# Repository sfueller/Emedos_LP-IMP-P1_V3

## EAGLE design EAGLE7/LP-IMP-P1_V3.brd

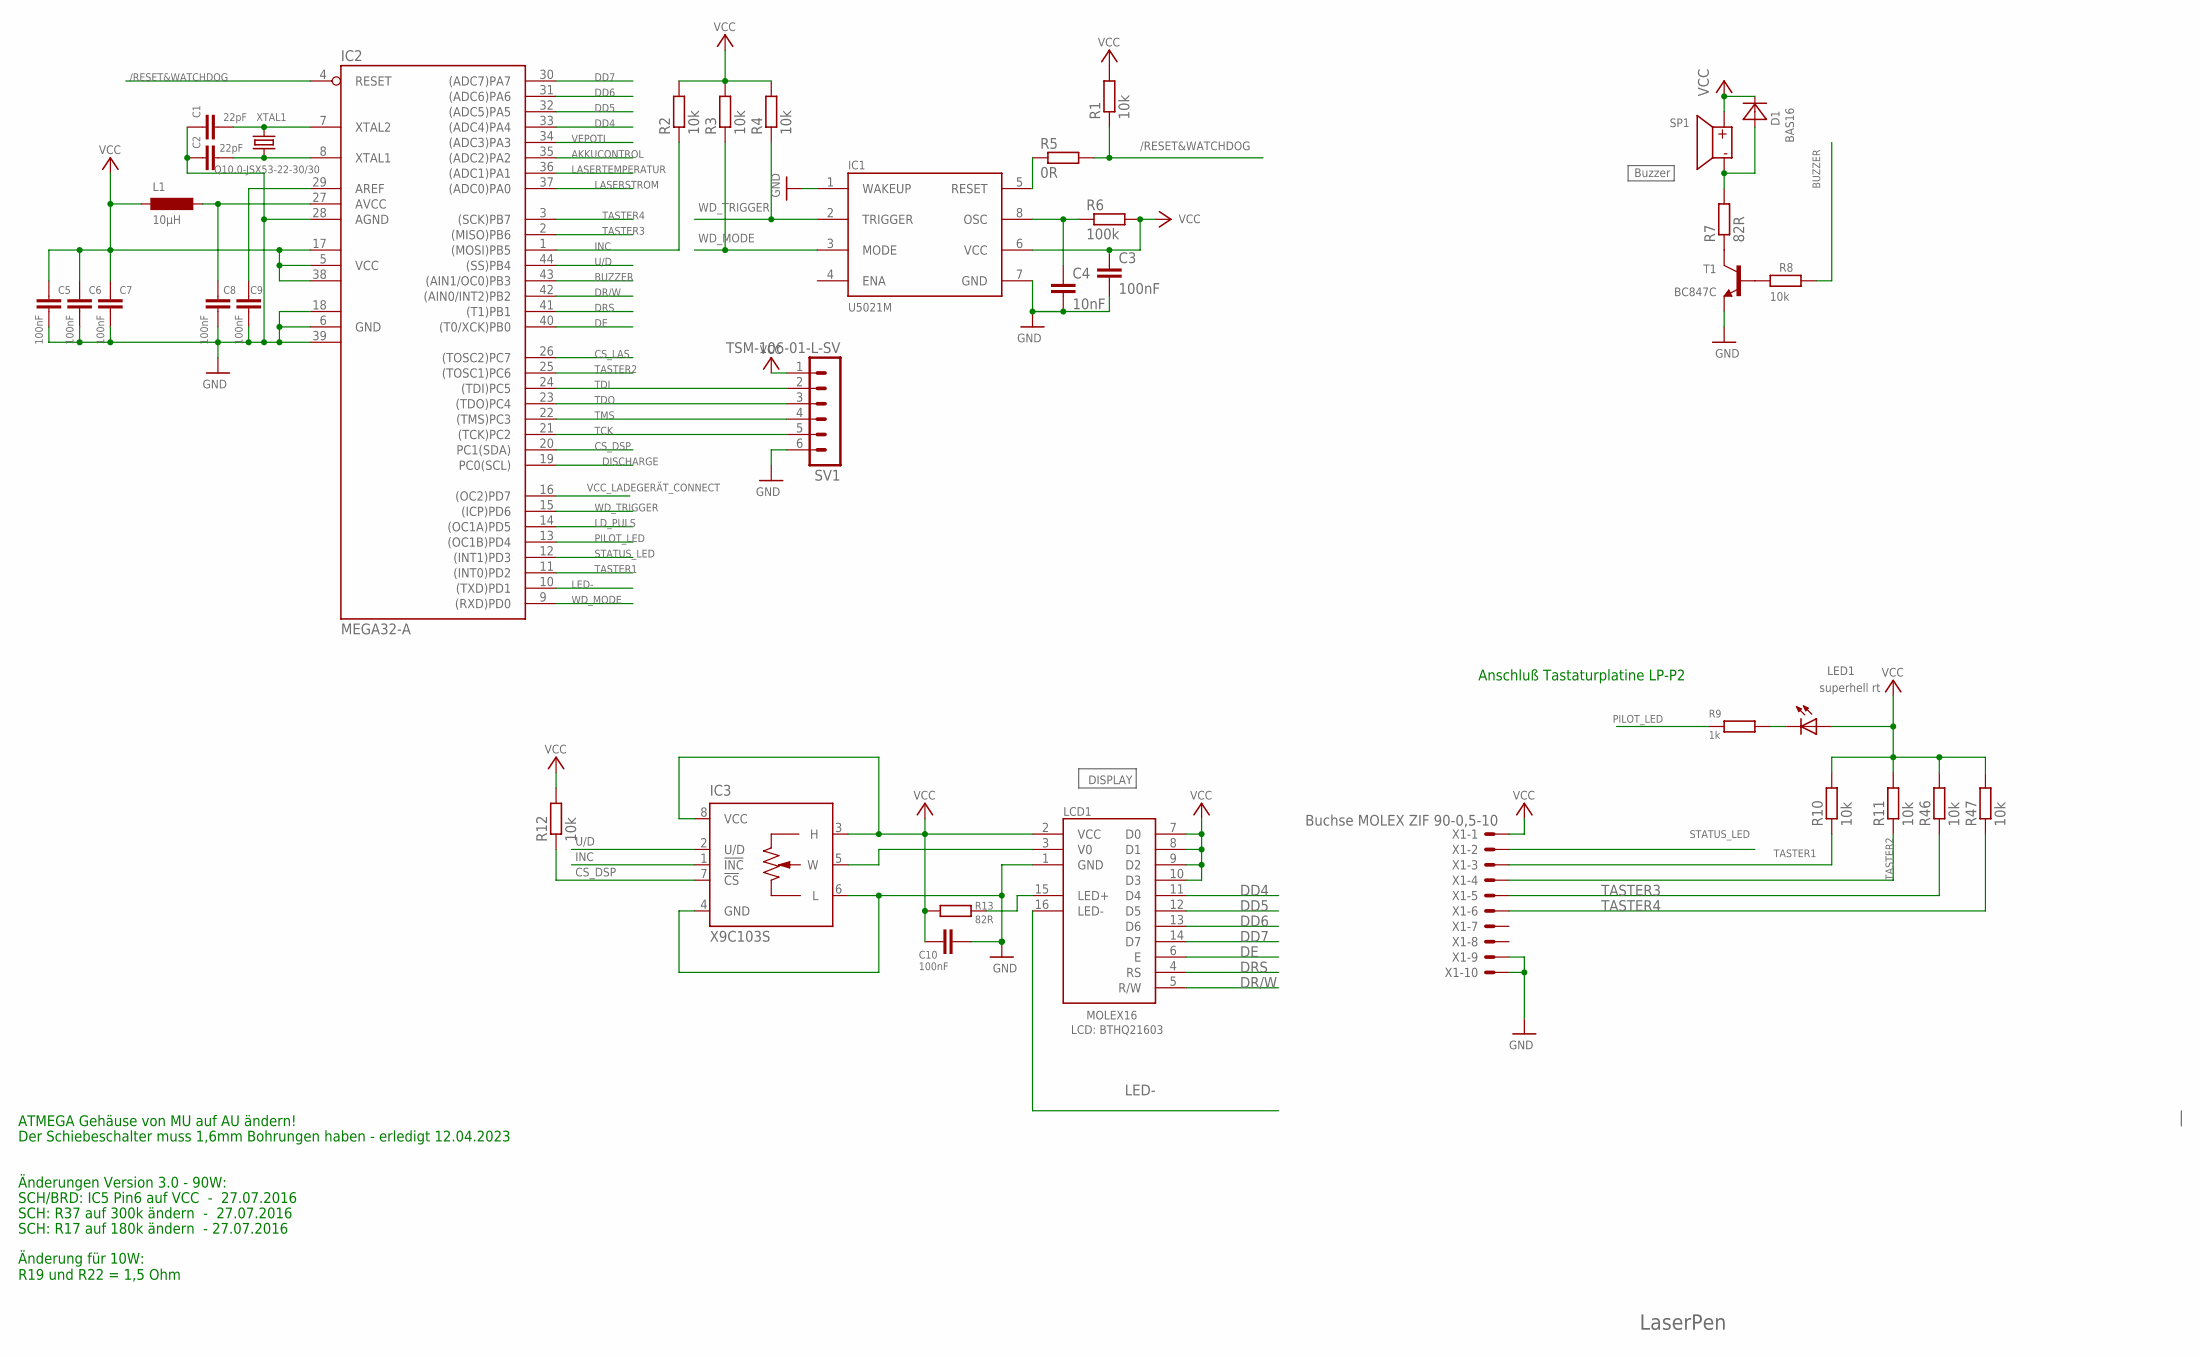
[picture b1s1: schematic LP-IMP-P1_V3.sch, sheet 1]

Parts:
C1, C2: 22pF; C0603
C3, C5, C6, C7, C8, C9, C10: 100nF; C0603
C4: 10nF; C0603
D1: BAS16; DIODE_SOT23
IC1: U5021M; SOIC8
IC2: MEGA32-A; TQFP44
IC3: X9C103S; SOIC08
L1: 10µH; R1210
LCD1: MOLEX16; MOLEX
LED1: superhell rt; LED3MM
R1, R2, R3, R4, R8, R10, R11, R12, R46, R47: 10k; R0603
R5: 0R; R0603
R6: 100k; R0603
R7, R13: 82R; MINI_MELF-0204R
R9: 1k; R0603
SP1: BUZZER
SV1: TSM-106-01-L-SV; MA06-1-SMD
T1: BC847C; SOT23
X1: Buchse MOLEX ZIF 90-0,5-10; 52745-1090
XTAL1: Q10.0-JSX53-22-30/30; JSX53

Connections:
/RESET&WATCHDOG: IC2.4 (RESET), R1.1, R5.2
AKKUCONTROL: IC2.35 ((ADC2)PA2); also elsewhere on the board
AREF: C9.1, IC2.29 (AREF)
AVCC: C8.1, IC2.27 (AVCC), L1.1
BUZZER: IC2.43 ((AIN1/OC0)PB3), R8.1
CS_DSP: IC2.20 (PC1(SDA)), IC3.7 (!CS), R12.1
CS_LAS: IC2.26 ((TOSC2)PC7); also elsewhere on the board
DD4: IC2.33 ((ADC4)PA4), LCD1.11 (D4)
DD5: IC2.32 ((ADC5)PA5), LCD1.12 (D5)
DD6: IC2.31 ((ADC6)PA6), LCD1.13 (D6)
DD7: IC2.30 ((ADC7)PA7), LCD1.14 (D7)
DE: IC2.40 ((T0/XCK)PB0), LCD1.6 (E)
DISCHARGE: IC2.19 (PC0(SCL)); also elsewhere on the board
DR/W: IC2.42 ((AIN0/INT2)PB2), LCD1.5 (R/W)
DRS: IC2.41 ((T1)PB1), LCD1.4 (RS)
GND: C1.1, C2.1, C3.2, C4.2, C5.2, C6.2, C7.2, C8.2, C9.2, C10.1, IC1.1 (WAKEUP), IC1.7 (GND), IC2.6 (GND), IC2.18 (GND1), IC2.28 (AGND), IC2.39 (GND2), IC3.4 (GND), IC3.6 (L), LCD1.1 (GND), SV1.6, T1.2 (E), X1.9, X1.10; also elsewhere on the board
INC: IC2.1 ((MOSI)PB5), IC3.1 (!INC), R2.1; also elsewhere on the board
LASERSTROM: IC2.37 ((ADC0)PA0); also elsewhere on the board
LASERTEMPERATUR: IC2.36 ((ADC1)PA1); also elsewhere on the board
LD_PULS: IC2.14 ((OC1A)PD5); also elsewhere on the board
LED+: LCD1.15 (LED+), R13.2
LED-: IC2.10 ((TXD)PD1), LCD1.16 (LED-)
unnamed: R7.1, T1.3 (C)
unnamed: C1.2, IC2.7 (XTAL2), XTAL1.3 (2)
unnamed: IC1.5 (RESET), R5.1
unnamed: C4.1, IC1.8 (OSC), R6.1
unnamed: LED1.K (C), R9.2
unnamed: C2.2, IC2.8 (XTAL1), XTAL1.1
unnamed: D1.1 (A), R7.2, SP1.-
unnamed: R8.2, T1.1 (B)
PILOT_LED: IC2.13 ((OC1B)PD4), R9.1
STATUS_LED: IC2.12 ((INT1)PD3), X1.2
TASTER1: IC2.11 ((INT0)PD2), R10.1, X1.3
TASTER2: IC2.25 ((TOSC1)PC6), R11.1, X1.4
TASTER3: IC2.2 ((MISO)PB6), R46.1, X1.5
TASTER4: IC2.3 ((SCK)PB7), R47.1, X1.6
TCK: IC2.21 ((TCK)PC2), SV1.5
TDI: IC2.24 ((TDI)PC5), SV1.2
TDO: IC2.23 ((TDO)PC4), SV1.3
TMS: IC2.22 ((TMS)PC3), SV1.4
U/D: IC2.44 ((SS)PB4), IC3.2 (U/D); also elsewhere on the board
V0: IC3.5 (W), LCD1.3 (V0)
VCC: C3.1, C5.1, C6.1, C7.1, C10.2, D1.3 (C), IC1.6 (VCC), IC2.5 (VCC), IC2.17 (VCC1), IC2.38 (VCC2), IC3.3 (H), IC3.8 (VCC), L1.2, LCD1.2 (VCC), LCD1.7 (D0), LCD1.8 (D1), LCD1.9 (D2), LCD1.10 (D3), LED1.A, R1.2, R2.2, R3.2, R4.2, R6.2, R10.2, R11.2, R12.2, R13.1, R46.2, R47.2, SP1.+, SV1.1, X1.1; also elsewhere on the board
VCC_LADEGERÄT_CONNECT: IC2.16 ((OC2)PD7); also elsewhere on the board
VEPOTI: IC2.34 ((ADC3)PA3); also elsewhere on the board
WD_MODE: IC1.3 (MODE), IC2.9 ((RXD)PD0), R3.1
WD_TRIGGER: IC1.2 (TRIGGER), IC2.15 ((ICP)PD6), R4.1

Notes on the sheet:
Buzzer
DISPLAY
LCD: BTHQ21603
LaserPen
Anschluß Tastaturplatine LP-P2
Änderungen Version 3.0 - 90W:
SCH/BRD: IC5 Pin6 auf VCC - 27.07.2016
SCH: R37 auf 300k ändern - 27.07.2016
SCH: R17 auf 180k ändern - 27.07.2016
Änderung für 10W: R19 und R22 = 1,5 Ohm
Der Schiebeschalter muss 1,6mm Bohrungen haben - erledigt 12.04.2023
ATMEGA Gehäuse von MU auf AU ändern!

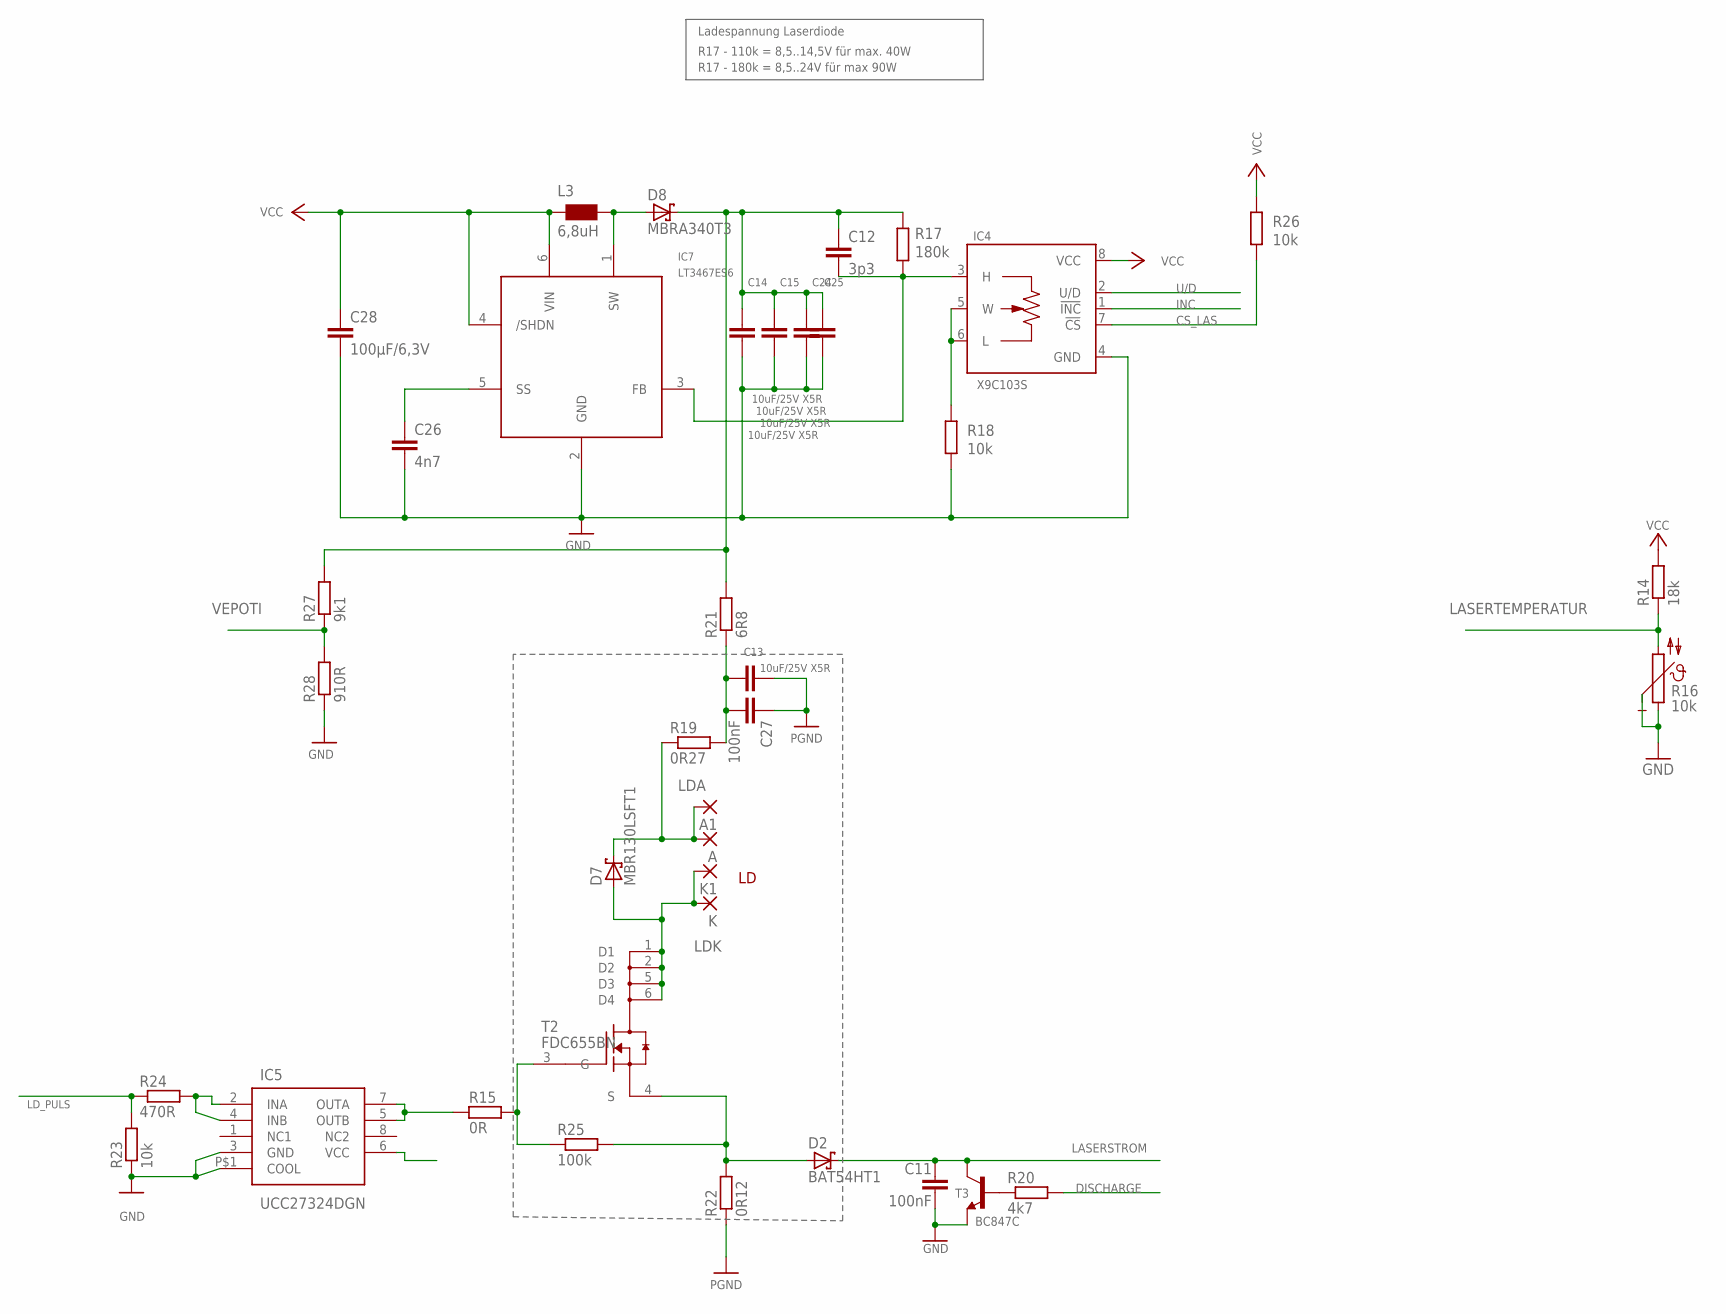
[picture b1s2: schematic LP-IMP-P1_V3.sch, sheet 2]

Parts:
A, A1: WIREPADSMD1,27-254; SMD1,27-2,54
C11, C27: 100nF; C0603
C12: 3p3; C0603
C13, C14, C15, C24, C25: 10uF/25V X5R; C1210K
C26: 4n7; C0603K
C28: 100µF/6,3V; C1210K
D2: BAT54HT1; SOD-323
D7: MBR130LSFT1; SOD-123LF
D8: MBRA340T3; SMA
IC4: X9C103S; SOIC08
IC5: UCC27324DGN; R-PDSO-G8
IC7: LT3467ES6; TSOT-23-6
K, K1: WIREPADSMD1,27-254; SMD1,27-2,54
L3: 6,8uH; WE-PD2_S
R14: 18k; R0603
R15: 0R; MINI_MELF-0204R
R16: 10k; R0805
R17: 180k; R0603
R18, R23, R26: 10k; R0603
R19: 0R27; MINI_MELF-0204R
R20: 4k7; R0603
R21: 6R8; MINI_MELF-0204R
R22: 0R12; MINI_MELF-0204R
R24: 470R; R0603
R25: 100k; R0603
R27: 9k1; R0603
R28: 910R; R0603
T2: FDC655BN; SUPERSOT-6
T3: BC847C; SOT23-BEC

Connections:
CS_LAS: IC4.7 (!CS), R26.1; also elsewhere on the board
DISCHARGE: R20.2; also elsewhere on the board
GND: C11.2, C13.2, C14.2, C15.2, C24.2, C25.2, C26.2, C27.1, C28.2, IC4.4 (GND), IC5.3 (GND), IC5.P$1 (COOL), IC7.2 (GND), R16.1, R18.1, R22.1, R23.1, R28.1, T3.E; also elsewhere on the board
INC: IC4.1 (!INC); also elsewhere on the board
LASERSTROM: C11.1, D2.C, T3.C; also elsewhere on the board
LASERTEMPERATUR: R14.1, R16.2; also elsewhere on the board
LDA: A.1, A1.1, D7.C, R19.1
LDK: D7.A, K.1, K1.1, T2.1 (D1), T2.2 (D2), T2.5 (D3), T2.6 (D4)
LD_PULS: R23.2, R24.1; also elsewhere on the board
unnamed: IC5.5 (OUTB), IC5.7 (OUTA), R15.1
unnamed: IC5.2 (INA), IC5.4 (INB), R24.2
unnamed: IC4.5 (W), IC4.6 (L), R18.2
unnamed: R20.1, T3.B
unnamed: C26.1, IC7.5 (SS)
unnamed: R15.2, R25.1, T2.3 (G)
unnamed: D8.A, IC7.1 (SW), L3.1 (2)
unnamed: C13.1, C27.2, R19.2, R21.1
unnamed: C12.2, IC4.3 (H), IC7.3 (FB), R17.1
U/D: IC4.2 (U/D); also elsewhere on the board
VCC: C28.1, IC4.8 (VCC), IC5.6 (VCC), IC7.4 (/SHDN), IC7.6 (VIN), L3.2 (1), R14.2, R26.2; also elsewhere on the board
VEPOTI: R27.1, R28.2; also elsewhere on the board
VPULS: C12.1, C14.1, C15.1, C24.1, C25.1, D8.C, R17.2, R21.2, R27.2
ZWISCHENWERT: D2.A, R22.2, R25.2, T2.4 (S)

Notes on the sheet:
Ladespannung Laserdiode
R17 - 110k = 8,5..14,5V für max. 40W
R17 - 180k = 8,5..24V für max 90W

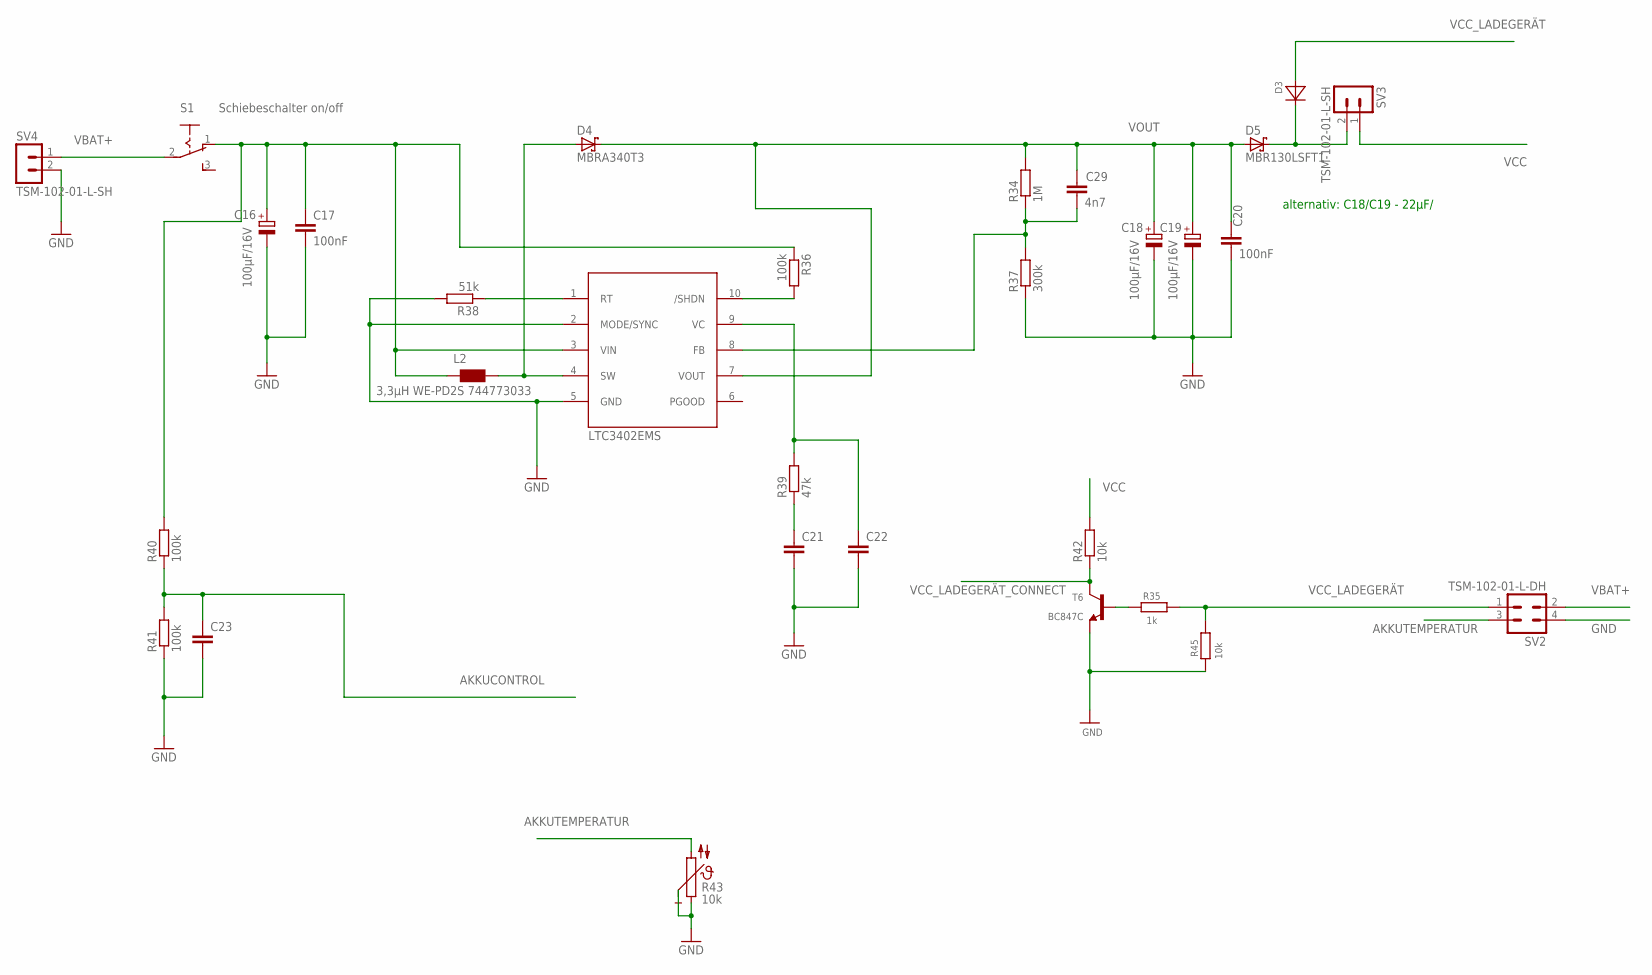
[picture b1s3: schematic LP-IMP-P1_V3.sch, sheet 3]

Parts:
C16, C18, C19: 100µF/16V; SMC_D
C17, C20, C23: 100nF; C0603K
C21: 1nF; C0603K
C22: 10pF; C0603K
C29: 4n7; C0603K
D3: BAS16; DIODE_SOT23
D4: MBRA340T3; SMA
D5: MBR130LSFT1; SOD-123LF
IC6: LTC3402EMS; MSOP-10
L2: 3,3µH WE-PD2S 744773033; WE-PD2_S
R34: 1M; R0603
R35: 1k; R0603
R36, R40, R41: 100k; R0603
R37: 300k; R0603
R38: 51k; R0603
R39: 47k; R0603
R42, R45: 10k; R0603
R43: 10k; R0805
S1: Schiebeschalter on/off; 255SB
SV2: TSM-102-01-L-DH; MA02-2-W-SMD
SV3, SV4: TSM-102-01-L-SH; MA02-1-W-SMD
T6: BC847C; SOT23

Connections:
AKKUCONTROL: C23.1, R40.1, R41.2; also elsewhere on the board
AKKUTEMPERATUR: R43.2, SV2.3
GND: C16.-, C17.2, C18.-, C19.-, C20.2, C21.2, C22.2, C23.2, IC6.2 (MODE/SYNC), IC6.5 (GND), R37.1, R38.2, R41.1, R43.1, R45.2, SV2.4, SV4.2, T6.2 (E); also elsewhere on the board
unnamed: D3.3 (C), D5.C, SV3.2
unnamed: R35.2, T6.1 (B)
unnamed: C29.2, IC6.8 (FB), R34.1, R37.2
unnamed: C22.1, IC6.9 (VC), R39.2
unnamed: C21.1, R39.1
unnamed: D4.A, IC6.4 (SW), L2.1 (2)
unnamed: IC6.1 (RT), R38.1
unnamed: IC6.10 (/SHDN), R36.2
VBAT+: S1.2, SV2.2, SV4.1
VCC: R42.2, SV3.1; also elsewhere on the board
VCC_LADEGERÄT: D3.1 (A), R35.1, R45.1, SV2.1
VCC_LADEGERÄT_CONNECT: R42.1, T6.3 (C); also elsewhere on the board
VIN: C16.+, C17.1, IC6.3 (VIN), L2.2 (1), R36.1, R40.2, S1.1 (O)
VOUT: C18.+, C19.+, C20.1, C29.1, D4.C, D5.A, IC6.7 (VOUT), R34.2

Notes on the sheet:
alternativ: C18/C19 - 22µF/

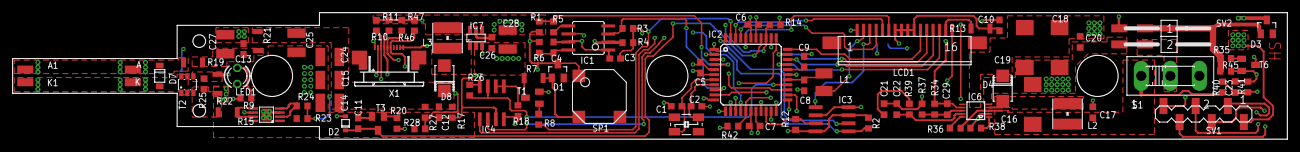
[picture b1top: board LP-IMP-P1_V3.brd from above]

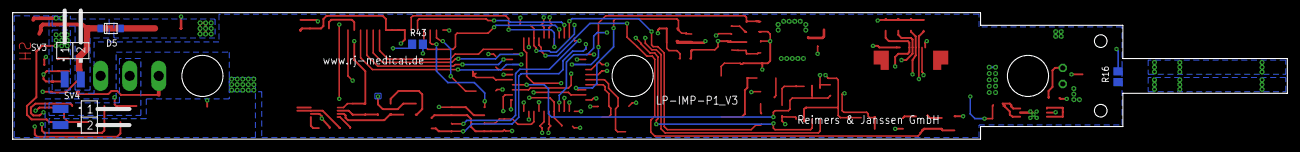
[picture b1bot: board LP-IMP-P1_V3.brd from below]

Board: 4 copper layers, 201.5 x 20.0 mm, 106 parts (5 on the bottom side), 73 nets.

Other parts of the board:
U$1: LASERPEN_IMP

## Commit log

2023-04-15 Update LP-IMP-P1_V3.brd, LP-IMP-P1_V3.sch, and 3 more files...
    Final Layout
